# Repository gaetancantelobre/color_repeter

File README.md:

Pi Pico (RP 2040) powered Simon Color game clone on a 41 mm coin footprint.
Code is free to use, modify,etc
Don't sell my design

Gerbers are available in the git.

Average cost per unit : 2.5 euros +- 0.2 euros.
Parts list :
 - pcb
 - 4x 6mm push button
 - 4x 1206 SMD LED
 - 5x 1206 220 Ohm Resistor
 - Pi Pico Zero (or clone, i use a aliexpress clone :)
 - 1x 5V piezo Buzzer

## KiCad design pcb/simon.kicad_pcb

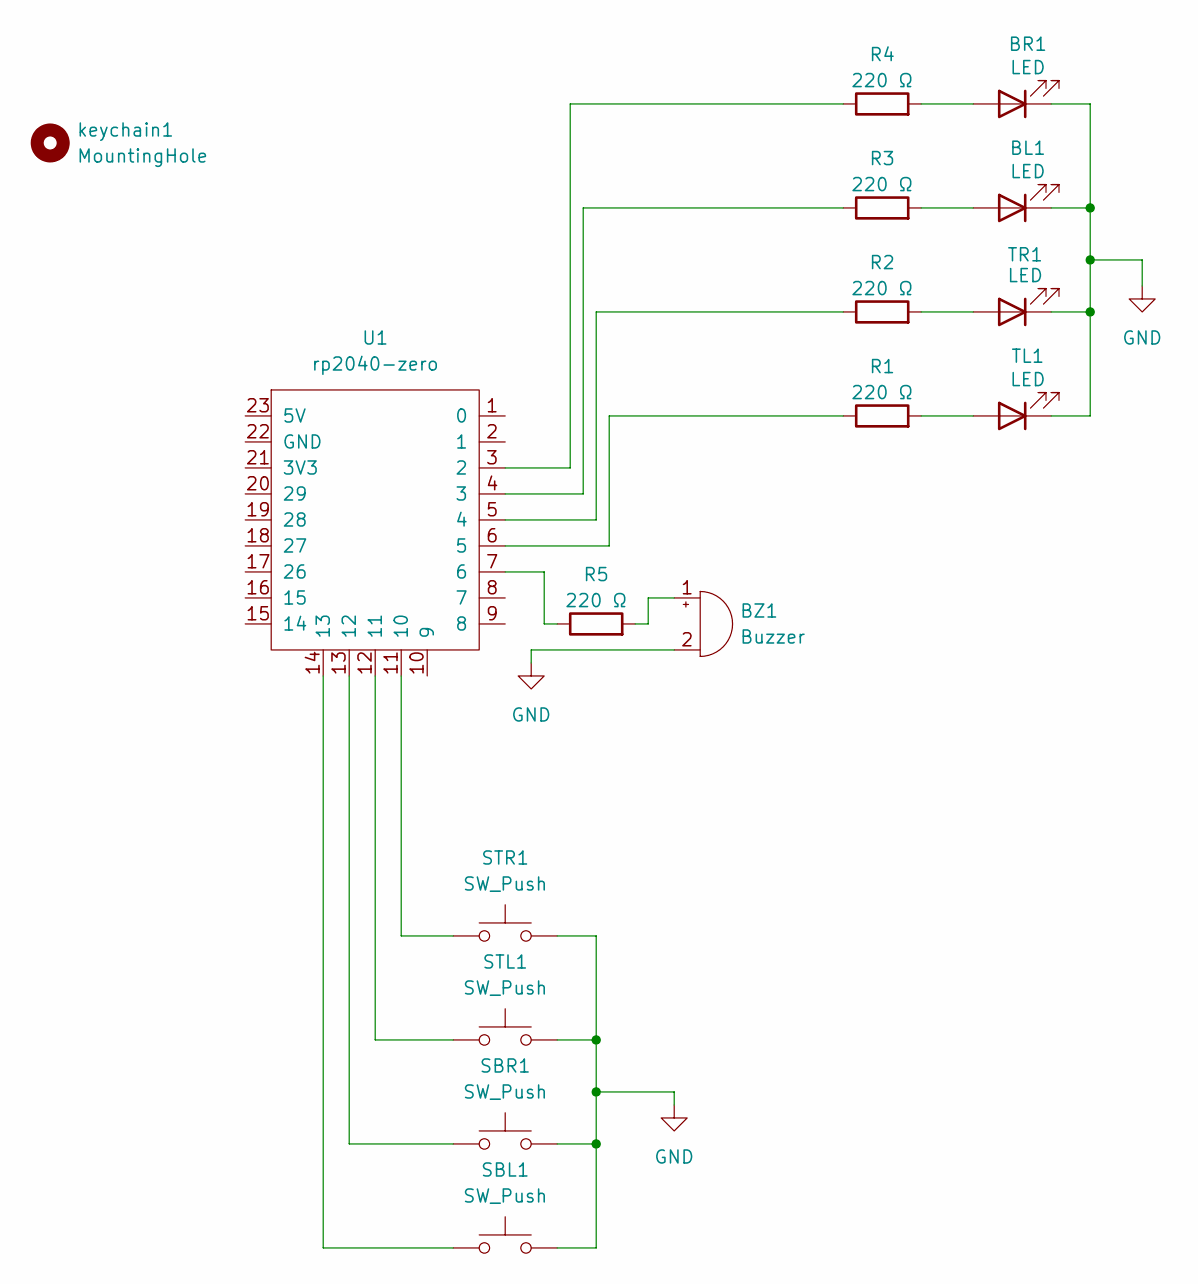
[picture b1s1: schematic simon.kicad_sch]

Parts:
BL1: LED; LED_1206_3216Metric_Pad1.42x1.75mm_HandSolder
BR1: LED; LED_1206_3216Metric_Pad1.42x1.75mm_HandSolder
BZ1: Buzzer; Buzzer_12x9.5RM7.6
R1, R2, R3, R4, R5: 220 Ω; R_1206_3216Metric_Pad1.30x1.75mm_HandSolder
SBL1: SW_Push; SW_PUSH_6mm
SBR1: SW_Push; SW_PUSH_6mm
STL1: SW_Push; SW_PUSH_6mm
STR1: SW_Push; SW_PUSH_6mm
TL1: LED; LED_1206_3216Metric_Pad1.42x1.75mm_HandSolder
TR1: LED; LED_1206_3216Metric_Pad1.42x1.75mm_HandSolder
U1: rp2040-zero; rp2040-zero-tht
keychain1: MountingHole; MountingHole_3.2mm_M3

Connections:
GND: BL1.1 (K), BR1.1 (K), BZ1.2 (-), SBL1.2, SBR1.2, STL1.2, STR1.2, TL1.1 (K), TR1.1 (K)
unnamed: BL1.2 (A), R3.2
unnamed: BR1.2 (A), R4.2
unnamed: BZ1.1 (+), R5.2
unnamed: R1.2, TL1.2 (A)
unnamed: R2.2, TR1.2 (A)
unnamed: R4.1, U1.3 (2)
unnamed: R3.1, U1.4 (3)
unnamed: R2.1, U1.5 (4)
unnamed: R1.1, U1.6 (5)
unnamed: R5.1, U1.7 (6)
unnamed: STR1.1, U1.11 (10)
unnamed: STL1.1, U1.12 (11)
unnamed: SBR1.1, U1.13 (12)
unnamed: SBL1.1, U1.14 (13)

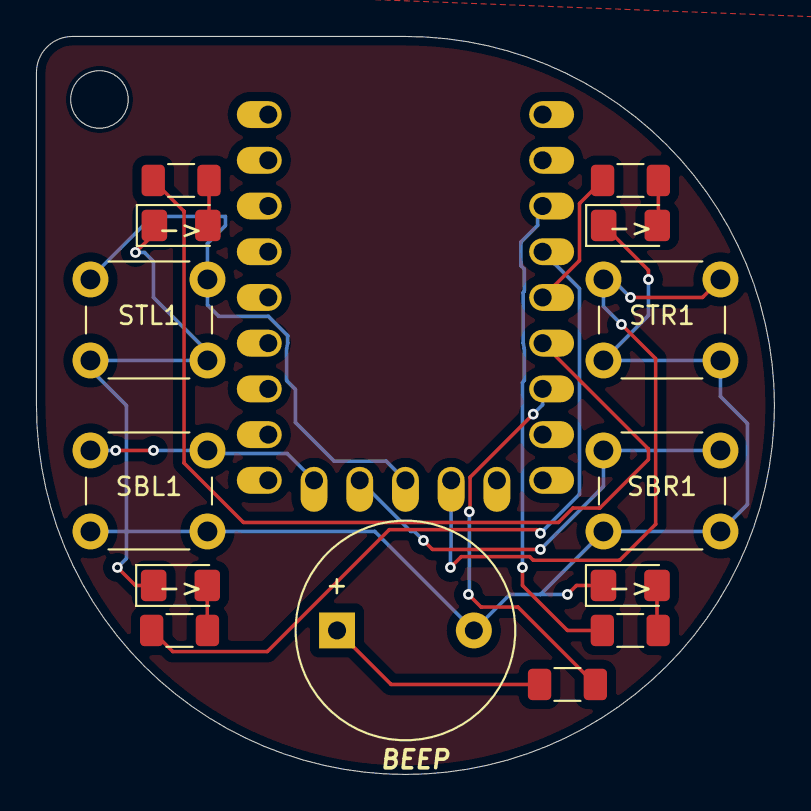
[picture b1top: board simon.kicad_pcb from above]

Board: 2 copper layers, 41.0 x 41.0 mm, 16 parts (0 on the bottom side), 15 nets.

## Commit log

2024-10-12 add pcb and code base
2024-10-14 added gerber files
2024-10-14 added basic game loop with out error treatement
2024-10-15 added basic readme
    including parts
    rights etx
2024-10-15 added full version
2024-10-15 updated gerbers and transition to pi pico
2024-10-20 fixed some bugs
2024-10-20 added better memory management
2024-10-20 added bound check for var
2024-10-27 cleaned repo and add .step files
2024-10-27 recleaned the git
